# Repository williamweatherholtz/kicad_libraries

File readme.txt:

Because KiCad, add
WILLIAM_3D as a path to this folder in the footprint PATHS
Reference it in future footprints with ${WILLIAM_3D}

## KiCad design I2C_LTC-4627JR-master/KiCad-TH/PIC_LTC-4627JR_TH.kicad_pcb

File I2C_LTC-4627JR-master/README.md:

# I2C control of a Lite-On LTC4627-JR (4-digit 7-segment LED)

The goal of this project is to create a small module that interfaces a 4-digit 7-segment LED to an I2C bus.

The original motivation is to allow a Raspberry Pi to display a few hexadecimal numbers with minimal overhead. Send a few bytes over I2C and this module will handle the rest.

Parts:

* The LED unit is the Lite-On LTC4627-JR. 
It has some features in addition to the standard 4-digit 7-segment design:
1. This is actually an 8-segment LED because of the 7-segments for numerals plus a LED for the optional decimal point.
2. This is actually a 5-digit display because of a few additional symbols on the surface. It appears to have been designed for a clock display so there are three additional LEDs controlled as a "fifth digit":  Two LEDs for displaying the ":" in 12:00 and a third probably to designate AM/PM.

* The brains of this operation will be a PIC 16F18345

* Current-limiting resistors * 8, one for each of the segments.

* NPN transistors * 5, one for each of the digits.

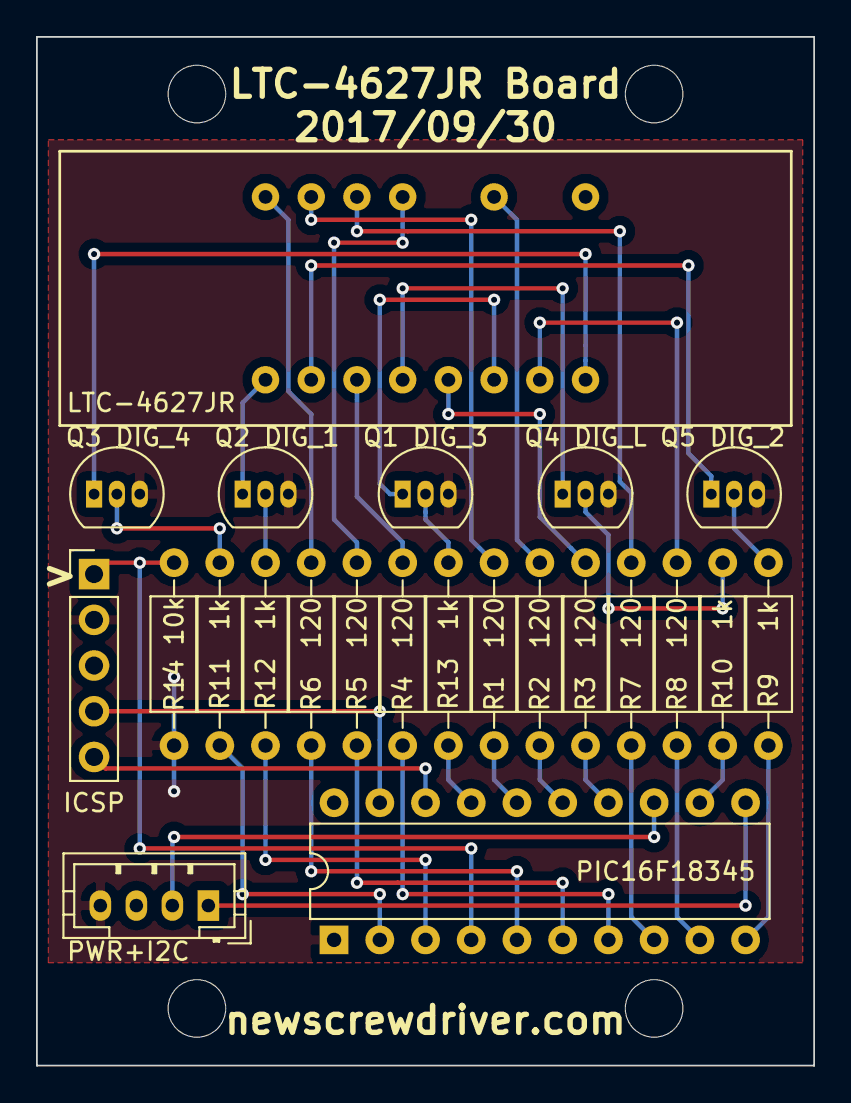
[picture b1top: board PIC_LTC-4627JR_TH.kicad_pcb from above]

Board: 2 copper layers, 43.2 x 57.2 mm, 27 parts (0 on the bottom side), 38 nets.

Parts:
H1, H2, H3, H4: MountingHole_3.2mm_M3
ICSP: Conn_01x05_Male; Pin_Header_Straight_1x05_Pitch2.54mm
LTC-4627JR: LTC-4627JR
PIC16F18345: PIC16F18344-P; DIP-20_W7.62mm
PWR+I2C: Conn_01x04; JST_PH_B4B-PH-K_04x2.00mm_Straight
Q1 DIG_3, Q2 DIG_1, Q3 DIG_4, Q4 DIG_L, Q5 DIG_2: Q_NPN_EBC; TO-92_Inline_Narrow_Oval
R1  120, R2  120, R3  120, R4  120, R5  120, R6  120, R7  120, R8  120: 120; R_Axial_DIN0207_L6.3mm_D2.5mm_P10.16mm_Horizontal
R9   1k, R10  1k, R11  1k, R12  1k, R13  1k: 1k; R_Axial_DIN0207_L6.3mm_D2.5mm_P10.16mm_Horizontal
R14 10k: 10k; R_Axial_DIN0207_L6.3mm_D2.5mm_P10.16mm_Horizontal

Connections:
/DIG_1: LTC-4627JR.1, Q2 DIG_1.1
/DIG_2: LTC-4627JR.2, Q5 DIG_2.1
/DIG_3: LTC-4627JR.6, Q1 DIG_3.1
/DIG_4: LTC-4627JR.8, Q3 DIG_4.1
/DIG_L: LTC-4627JR.4, Q4 DIG_L.1
/I2CCL: PIC16F18345.11, PWR+I2C.1
/I2CDA: PIC16F18345.13, PWR+I2C.2
/ICSPCLK: ICSP.5, PIC16F18345.18
/ICSPDAT: ICSP.4, PIC16F18345.19
/VPP: ICSP.1, PIC16F18345.4, R14 10k.1
GND: ICSP.3, PIC16F18345.20, PWR+I2C.3
unnamed: LTC-4627JR.3, R4 120.1
unnamed: LTC-4627JR.5, R3 120.1
unnamed: LTC-4627JR.7, R8 120.1
unnamed: LTC-4627JR.11, R2 120.1
unnamed: LTC-4627JR.13, R5 120.1
unnamed: LTC-4627JR.14, R7 120.1
unnamed: LTC-4627JR.15, R1 120.1
unnamed: LTC-4627JR.16, R6 120.1
unnamed: Q1 DIG_3.2, R13 1k.1
unnamed: Q2 DIG_1.2, R12 1k.1
unnamed: Q3 DIG_4.2, R11 1k.1
unnamed: Q4 DIG_L.2, R10 1k.1
unnamed: Q5 DIG_2.2, R9 1k.1
unnamed: PIC16F18345.16, R1 120.2
unnamed: PIC16F18345.15, R2 120.2
unnamed: PIC16F18345.14, R3 120.2
unnamed: PIC16F18345.7, R4 120.2
unnamed: PIC16F18345.6, R5 120.2
unnamed: PIC16F18345.5, R6 120.2
unnamed: PIC16F18345.8, R7 120.2
unnamed: PIC16F18345.9, R8 120.2
unnamed: PIC16F18345.10, R9 1k.2
unnamed: PIC16F18345.12, R10 1k.2
unnamed: PIC16F18345.2, R11 1k.2
unnamed: PIC16F18345.3, R12 1k.2
unnamed: PIC16F18345.17, R13 1k.2
VCC: ICSP.2, PIC16F18345.1, PWR+I2C.4, Q1 DIG_3.3, Q2 DIG_1.3, Q3 DIG_4.3, Q4 DIG_L.3, Q5 DIG_2.3, R14 10k.2

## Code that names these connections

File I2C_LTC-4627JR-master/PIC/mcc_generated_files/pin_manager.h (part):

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// get/set DIG_3 aliases
#define DIG_3_TRIS               TRISAbits.TRISA2
#define DIG_3_LAT                LATAbits.LATA2
#define DIG_3_PORT               PORTAbits.RA2
#define DIG_3_WPU                WPUAbits.WPUA2
#define DIG_3_OD                ODCONAbits.ODCA2
#define DIG_3_ANS                ANSELAbits.ANSA2
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// get/set DIG_1 aliases
#define DIG_1_TRIS               TRISAbits.TRISA4
#define DIG_1_LAT                LATAbits.LATA4
#define DIG_1_PORT               PORTAbits.RA4
#define DIG_1_WPU                WPUAbits.WPUA4
#define DIG_1_OD                ODCONAbits.ODCA4
#define DIG_1_ANS                ANSELAbits.ANSA4
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// get/set DIG_4 aliases
#define DIG_4_TRIS               TRISAbits.TRISA5
#define DIG_4_LAT                LATAbits.LATA5
#define DIG_4_PORT               PORTAbits.RA5
#define DIG_4_WPU                WPUAbits.WPUA5
#define DIG_4_OD                ODCONAbits.ODCA5
#define DIG_4_ANS                ANSELAbits.ANSA5
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// get/set DIG_L aliases
#define DIG_L_TRIS               TRISBbits.TRISB5
#define DIG_L_LAT                LATBbits.LATB5
#define DIG_L_PORT               PORTBbits.RB5
#define DIG_L_WPU                WPUBbits.WPUB5
#define DIG_L_OD                ODCONBbits.ODCB5
#define DIG_L_ANS                ANSELBbits.ANSB5
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// get/set DIG_2 aliases
#define DIG_2_TRIS               TRISBbits.TRISB7
#define DIG_2_LAT                LATBbits.LATB7
#define DIG_2_PORT               PORTBbits.RB7
#define DIG_2_WPU                WPUBbits.WPUB7
#define DIG_2_OD                ODCONBbits.ODCB7
#define DIG_2_ANS                ANSELBbits.ANSB7
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
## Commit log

2018-11-09 Added README.md, .gitignore (KiCAD) files
2018-11-09 init
2018-11-15 added several libraries, parts, 3d, reorganized
2018-11-20 added dc/dc parts
2018-12-04 fix encoder footprint
2018-12-05 removed scripts sub
2018-12-05 add scripts submodule for validating KLC compliance
2019-01-09 added many parts, libraries
2019-01-18 changed structure
2019-03-04 ch-ch-changes
2019-03-06 updating library
2019-03-06 complete restructuring
2019-03-06 removed scripts submodule
2019-03-07 restructuring libraries
2019-04-24 added digikey repo
2019-10-02 added terminal blocks, better and more consistent 3D models, some sensors
2019-10-02 removed DK sub
2019-10-07 adieu obsolete files. cleaning up
2019-11-01 added courtyards on some new phoenix termination blocks
2019-11-15 added Phoenix Contact ZFKDS-W-5.08mm wire2board series connectors
2019-11-15 removed redundant footprint
2019-12-10 added switches, ws2813 LED
2019-12-11 added some more LCSC parts, USB C in-board connector
2019-12-16 modified LED lib
2020-01-09 removed stm32 unofficial
2020-01-25 added diode pkg
2020-01-25 added footprint & 3d Parts for LoRa board
2020-01-25 changed absolute path to one relative to WILLIAM_3D
2020-01-25 fully updated, I think
2020-02-08 added jst library and AX series connectors
2020-02-22 added RN52 bluetooth audio module & library
2020-03-05 added dac library & symbol
2020-03-06 Rename readme.txt.txt to readme.txt
2020-03-06 removed renaming script, that was used to clean up library references
2020-05-19 8ch logic level converter
2020-05-28 added package, fix stm32f446 mic
2020-06-03 added &updated parts for dataloggerv2
2020-06-04 fixed batteries, +- -> 1,2
2020-06-11 new connectors for dow luge board and max_led board
2020-07-07 some redundants removed
2020-10-04 merging libs
2020-10-10 items for milad board
2020-10-12 TG board parts
2020-10-12 added 40 pin molex FFC
2020-10-12 4 pin amphenol for newhaven disp
2020-10-12 PowerDI123 type B footprint added (REVERSE polarity from std)
2020-10-13 fixed dc dc. was using unnecessary footprints
2020-10-14 added good 10V FET low RDSon
2020-10-14 fixed FET
2020-10-15 bad 3d ref
2021-01-04 updates for TouchGFX board
2021-03-08 added stm32f746DISCO connectors
2021-05-06 more parts for display connectivity
2021-05-13 add mechanical to fp
2022-04-18 new parts?
2022-06-23 backup tx
2022-09-19 added high-side FET drivers, lots of cleanup
2022-10-03 fix connector footprints
2023-01-03 new parts for 2022 CRIs
2023-03-14 hmi update
2023-12-13 parts for load cell board

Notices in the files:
I2C_LTC-4627JR-master/PIC/mcc_generated_files/pin_manager.h:
Copyright (c) 2013 - 2015 released Microchip Technology Inc.  All rights reserved.
